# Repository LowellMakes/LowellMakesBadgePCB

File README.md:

# LowellMakesBadgePCB
Let's make a badge PCB for soldering classes and swag!

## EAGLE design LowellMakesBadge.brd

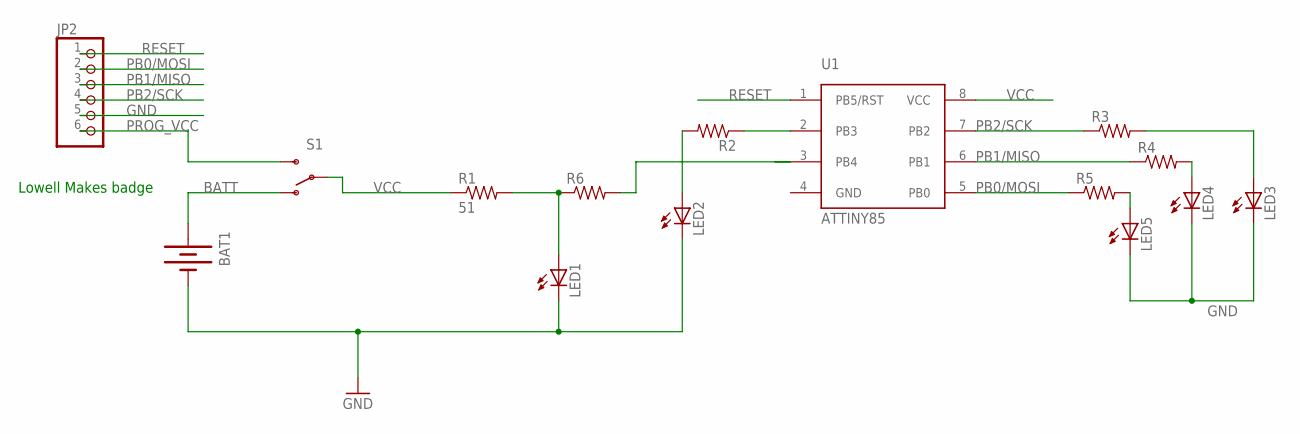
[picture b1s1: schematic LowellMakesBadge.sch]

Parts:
BAT1: BATTERY12PTH; BATTCON_12MM_PTH
JP2: PINHD-1X6; 1X06
LED1: LED5MM
LED2, LED3, LED4, LED5: LEDCHIP-LED0805; CHIP-LED0805
R1: 51; AXIAL-0.3
R2, R3, R4, R5, R6: RESISTOR; 0805
S1: SWITCH-SPDTPTH; SWITCH-SPDT
U1: ATTINY85; SOIC8

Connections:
BATT: BAT1.VCC@1 (+), S1.1 (O)
GND: BAT1.GND (-), JP2.5, LED1.K (C), LED2.C, LED3.C, LED4.C, LED5.C, U1.4 (GND)
unnamed: LED1.A, R1.P$2 (2), R6.1
unnamed: R6.2, U1.3 (PB4)
unnamed: LED5.A, R5.2
unnamed: R2.1, U1.2 (PB3)
unnamed: LED2.A, R2.2
unnamed: LED4.A, R4.2
unnamed: LED3.A, R3.2
PB0/MOSI: JP2.2, R5.1, U1.5 (PB0)
PB1/MISO: JP2.3, R4.1, U1.6 (PB1)
PB2/SCK: JP2.4, R3.1, U1.7 (PB2)
PROG_VCC: JP2.6, S1.3 (S)
RESET: JP2.1, U1.1 (PB5/RST)
VCC: R1.P$1 (1), S1.2, U1.8 (VCC)

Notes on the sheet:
Lowell Makes badge

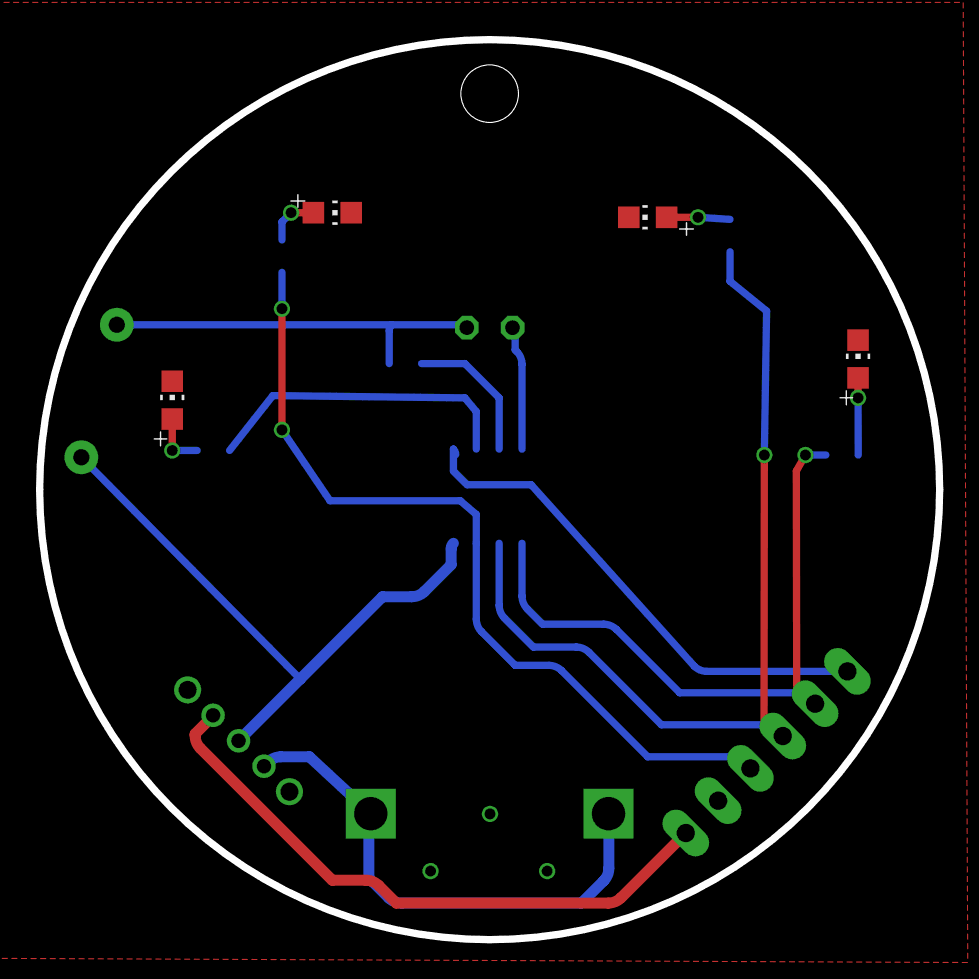
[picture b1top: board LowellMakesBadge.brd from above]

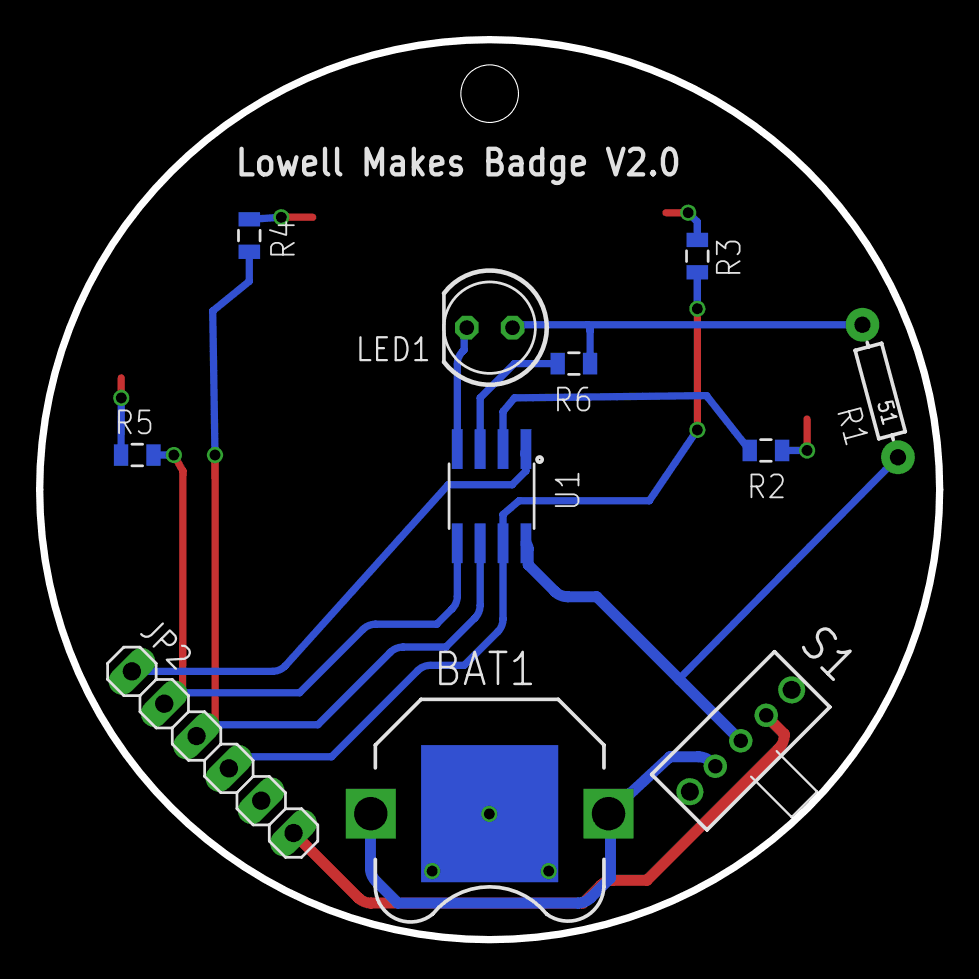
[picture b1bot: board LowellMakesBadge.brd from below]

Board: 2 copper layers, 50.0 x 50.0 mm, 16 parts (11 on the bottom side), 15 nets.

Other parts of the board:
U$1: LOWELLMAKES-LOGO2

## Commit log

2015-06-23 Adding first version created by @sajingeo
2015-06-23 Adding next version from @sajingeo including a 3d model
2015-06-24 Created Very Simple First Version. Should put copper text with version on the back
2015-06-24 Updated battery to be through hole and added text. Need to add stop
2015-06-24 Added mask stop for text
2015-06-24 Adding Gerbers for V1.0
2015-06-25 More updates from @sajingeo
2015-06-25 Updated board to change version from 1 to 2.0
2016-07-06 Made a bunch of changes to add support for AT Tiny 85
2016-07-06 Updates to use all at tiny pins (last GPIO to control main through hole LED as well
2016-07-07 Updates to wire in a full programming header. moved SMD led pins around to simplify routing
2016-07-07 Cleaned up the battery power signal and passed some DRC tests
2016-07-11 Update to make board render properly in 3d model
2016-07-11 Update to name micro as U1 instead of U$2
2016-07-11 Fixing silkscreen on back of board to be on the right layer. Updated 3d images
2016-07-11 Updating gerber files for submission to Seeed Studio

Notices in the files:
parts and their libraries:
SparkFun: Licensing: CC v3.0 Share-Alike You are welcome to use this library for commercial purposes.
